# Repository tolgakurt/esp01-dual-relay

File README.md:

# Introduction

This project is about a dual channel relay circuit driven by an ESP8266-01 IC which connects to Azure IoT Hub. The device can be controlled by a progressive web app which communicates with serverless Azure functions in the backend which then communicates with the IoT Hub. We developed and built the circuit, and implemented the code nearly from scratch.  

This is a pet project and we aimed to build a nice gadget, but we also aimed to learn new things; so we implemented features and took precautions which are hardly necessary. So expect more detail than required. You may also find some already marketed products for that purpose, but they lack this feature or that we think that we must have, and moreover, where is the fun using such a product directly?  

This project began when we first encountered a specific type of curtain which is opened and closed by an AC motor. If you haven't encountered them yet, there are curtains which are like projector curtains in shape, which also include a cylindirical motor in the shaft that collects the curtain which can turn both ways depending on which input line of the motor is connected to AC phase line. The motor has 4 connections: 1 for ground, 1 for neutral, 2 for phase. One of the phase connections rotates the motor clock-wise and the other rotates anti clock-wise. So, why not develop a circuit that controls this curtain?  

We implemented this project with [Kutalmış İnce](http://kutalmisince.com/) and mobilized the curtains in our bedrooms so that they can be dynamically programmed by a mobile app to open up at (say) 7AM (best way to wake up gracefully) and close down at (say) 6PM, or can be opened or closed at the moment. We also wanted them to be manually controllable via simple switches. This became a long journey in which we first developed a master/slave configuration where a Raspberry Pi acted as the main hub directing some Atmel based controllers. We would put Raspberry Pi in close proximity of the router so that it can be accessed online, and it will connect with the controllers using nRF24L01+ ICs. However it became a bit expensive, and we thought that we could construct the same system using ESP8266 so that we get rid of slave/master configuration. This was cheaper and working, but we were using nodeMCU devboards (which use ESP8266-12 IC with lots of GPIO pins) and this could still get cheaper by using ESP8266-01 modules. This wasn't easy as said, since ESP8266-01 is a very limited and delicate (and almost unstable) module. Rest of this document and other documents in the folders explains the whole procedure to get such a system up and running steady.  

We tried to be sure about all the components we used and each line of code we wrote, but please comment if you notice something wrong or inappropriate. Needless to say, what we developed is a relay circuit controlled online, which means you can control any common AC (or DC, for that matter) utility with it.  

## The Circuit

We modeled the circuit using EAGLE. The details about the design and implementation of the circuit can be found in `pcb` folder. This folder also contains gcode files so that you can etch the pcb using a CNC machine. You can export the trace masks from EAGLE as well. More information can be found [here](pcb).  

## Embedded Code and Azure IoT Hub 

Embedded code is contained in `esp` folder. This software connects the device to Azure IoT Hub using MQTT protocol. An overall and detailed information can be found [here](esp).  

## Azure Functions and Storage

Azure Functions are implemented to handle user requests and manage the devices in the IoT Hub. All related files are in `azureFunctions` folder. The details about Azure Functions, related Azure Storage, and implemented API endpoints are defined [here](azureFunctions).  

## User Interface

A frontend for the users is implemented as a progressive web app. Frontend files are in `frontend` folder. The usage details and business logic of the user interface are explained [here](frontend).  

## Possible Enhancements

1. Use a 5V power supply and design a 3V3 voltage regulator phase (using LM1117-3V3) to power up ESP-01. At the current version, the main source of the instability of the circuit is the voltage spikes generated by the relay coils when they are triggered and released. Now, a zener-rectifier combination is used to dissipate coil charge and a zener-capacitor combination is used to smooth and clamp the voltage before ESP-01. However, a regulator will do that better than a zener-capacitor couple. (And according to a rumor, 5V relays create less spikes when they are triggered and released.) However, this change also effects the driving transistors. When the GPIO pins are high, they are 3V3. But the relays should be triggered using 5V. If we use a single PNP in that condition, the transistor will always be open since (5V - 3V3 = 1V7 > 0V6). So, we need to shift 3V3 to 5V with a Sziklai pair, where the first transistor is a PNP fed with 3V3 and triggers the base of the second transistor which is an NPN which is fed with 5V and drives the relays. On the other side, this configuration will render diodes connected to the GPIO pins useless, so we can get rid of them.  

2. No matter how well the code is written and how reliable the electronic components and the design, the circuit can become unresponsive after a while for this or that reason. So, an additional hardware watchdog built with 555 may restart the device in such a condition. A good design can be found [here](http://upperbound.com/projects/555-watchdog-timer/). Basically, what we need to do is to trigger 555 periodically from ESP-01 so that its countdown timer is reset. If we don't, it will trigger the `RST` pin of the ESP-01 after a while, which will cause a hard reset and the device hopefully becomes responsive again. The countdown resetting signal should be done as a result of a successful `pong` for a `ping` to Azure IoT Hub, so that we ensure that the device will restart if the device loses connection with Azure IoT Hub. However, there may be internet disconnections for a while, so we should let the hardware watchdog wait for a reasonable amount time before it restarts ESP-01.

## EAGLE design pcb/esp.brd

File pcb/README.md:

# The Schematic

We modeled the circuit using EAGLE. However, the devices used in the circuit model file is coming from my custom devices library. You need to have this library introduced to EAGLE beforehand. The library can be found [here](https://github.com/tolgakurt/eagle-parts-library).  

The schematic of the circuit is as such:  

## AC Line

The circuit does not include a power supply, so you need to have a 3.3V DC output power supply rated with at least 500mA. We are using [this circuit](https://www.banggood.com/AC-DC-3_5W-Isolated-AC-110V-220V-To-DC-3_3V-1A-Switch-Power-Supply-Converter-Module-p-1088504.html?rmmds=buy&cur_warehouse=CN). You need to connect your AC line to the `ACIN` connector and you can also connect parallel cables to the input rail of the power supply from `ACIN`. `ACOUT` connector will deliver power up to two devices. We use one pin in `ACOUT` connector to open the curtain, and the other to close. The last one goes to the neutral line of the motor. You can also use one more pin in each connector to connect the ground cable.  

## DC Line

As I mentioned, the power is supplied by an external circuit. This circuit has a single input at `3V3IN` connector for all the components. Generally it is a better practice to isolate the relays from the driver circuit because of the voltage spikes generated by the coil in the relay with the help of an optocoupler, but this necessitates a secondary power source. However, we wanted to keep this simple and cheap. More on spike protection below.  

## Powering Up ESP-01

ESP-01 is a small and cheap IC, and has only 2 GPIO pins which is barely enough for a simple project like this. Moreover, these IO pins are also used to determine the boot mode. More on this subject [here](https://www.forward.com.au/pfod/ESP8266/GPIOpins/ESP8266_01_pin_magic.html).  

Basically, you need to pull both IO pins high to boot from SPI flash (which is the normal operating mode). So, you need to connect these pins to 3V3 rail using resistors. In the article linked above, 3K3 resistors are adviced, however, during our tests, We found out that 3K3 may not be strong enough to pull IO pins high. Using 3K3, something like 1 in 10, ESP-01 couldn't start from SPI flash. So, we tried again using 2K2, and found that it always booted correctly. We are not entirely sure about the reason, please correct us on this if we're mistaken.  

You need to connect `VCC` pin to 3V3 rail and GND pin to ground directly. It is also a good practice to pull `CH_PD` and `RST` pin high, so we connected them to 3V3 rail via 3K3 resistors. Moreover to that, we connected `RST` pin to ground via a 100uF capacitor to prevent the device from boot during power up phase for a short period, till the supply rail becomes steady. Also, `SWRST+` pin is connected to `RST` pin, so that you can connect a switch in between this and `SWRST-` pin and reset the device with that.  

The GPIO pins are used to drive the relays, but we also needed an input to reset the WiFi configuration of the ESP-01 in case of a configuration change in WiFi. So, we used `RX` pin as a pullup input. When `RX` pin is initialized as `INPUT_PULLUP`, it is internally pulled high weakly. To be sure, we also connected it to 3V3 rail with a 3K3 resistor. If you connect a switch in between `SWRX+` pin and `SWRX-` and close this switch, RX pin will read low and then you can reset the WiFi configuration. A pin is also connected to `TX` to be able to connect to the device and view the logs in serial monitor while debugging.  

In addition to the power supply, it is always a good practice to put some decoupling capacitors close to `VCC` and `GND` pins of ESP-01, so we included a 15pF and a 100nF capacitors. More than that, we observed that the power supply cannot function steadily when the relays are clicking, so we placed a 220uF capacitor and a 3V3 zener parallel to the decoupling capacitors to clamp and smooth the voltage spikes which dramatically enhanced the stability of ESP-01.  

## Driving Relays

ESP-01 cannot drive the relays directly since it can source only 12mA current, which is not enough to activate the relays. So, there needs to be a transistor in between to control the current over the relays, and these transistors need to be PNP type because their base are connected to GPIO pins which are inevitably connected to 3V3. In this configuration, `IO0` and `IO2` are pulled high in the beginning of ESP-01 `setup` function and when a relay needs to be activated, connected GPIO pin is pulled low.  

At first, we were driving the relays using only the transistors and ESP-01, but we thought that it would be nice to have some buttons or switches, which can also control the relays in parallel to ESP-01. This is somehow a very handy feature since your ESP-01 may become bricked or you cannot (or don't want to) reach ESP-01 over WiFi. `SW1+` and `SW2+` pins are introduced for this reason. So that, you can connect a switch in between these pins and `SW12-` pin, which goes to ground, and pull the base of the transistors low and activate the transistors. But you need to prevent the current flowing from `IO0` and `IO2` to ground. For this reason, there are `D1` and `D2` in between, which prevents flow in that direction.  

The relays we used are triggered at 3V and they use a current of 105mA to operate. For the spike protection, we used a reverse-biased diode in combination with a 3V3 zener. Generally, a single diode is advised, but an additional zener helps to extend relay life as described [here](https://www.te.com/commerce/DocumentDelivery/DDEController?Action=srchrtrv&DocNm=13C3264_AppNote&DocType=CS&DocLang=EN).  

Parallel to the relays and spike suppression components, there is a low-power led, which is used to indicate if the relay is switched on. These leds are known to have a forward voltage of 2.0V, so they will leave 1.3V behind. They need a current in between 5-20mA, so a 100R resistor will let 13mA to pass, which is OK.  

So, we require a total current of about 120mA and the transistors should let that. We used 2N3906 transistors since they can support a collector current of 200mA continuously. They are commonly found and are very cheap. You can also use something like 2N2222 which lets 1A to pass. But beware of using some other commonly found transistors like BC557 since they are rated as 100mA max.  

We will use these transistors not in linear region, but in saturation mode as simple switches. So, we need to determine the base current using the gain characteristics of 2N3906. [In its datasheet](https://www.sparkfun.com/datasheets/Components/2N3906.pdf), it says that the minimum gain is 30 when the collector is at 100mA and Vce is 1V. We access the base via a diode, so we have a drop of 0.7V there. The base needs to be 0.7V lower than the emitter. Thus we have 3.3V - 0.7V - 0.7V = 1.9V left. This is close to 1V, so we will assume the minimum gain suggested in the specs: 30.  

We need to have a current of 120mA in the collector, thus we need 4mA in the base which can be ensured with a 470R base resistor. On the other hand, 4mA is safely less than 12mA, which is the recommended sink current limit of ESP-01 GPIO pins.  

The switch does not pass over a diode as the GPIO pins, so it will introduce slightly more current to the base, which is not a problem.  

# The Board

As I mentioned, the components used in the circuit model file is coming from my custom devices library. I developed this library to create custom packages that fits [my custom made CNC machine](https://github.com/tolgakurt/my-custom-cnc). DRC rules, pad diameters, trace widths are all set according to the specs of this machine. Finally, the board we created is for a single-sided PCB and looks as such:  

Let me remind you that this circuit involves high voltage AC application, so please take necessary precautions before getting your hands dirty.  

## Etching

`.sch` and `.brd` files are in this directory, so you can create the etching mask if you are using chemicals to create the nets. We used my custom made CNC machine, so we generated gcode using the `PCB-GCode` plugin. You can find related information [here](http://www.richa1.com/RichardAlbritton/create-g-code-from-an-eagle-file/). The gcode generated by this plugin is also given in `gcode` folder. You can use them if somehow your device is similar to mine.  

The teal colored lines represent the milling routes with 0.5mm of depth and 1mm of width. These lines are used to isolate the AC line from the DC part better. They also isolate AC lines from each other. With these lines in place, you can actually delete the trace lines carrying AC.  

The same teal colored lines also indicate the outer frame, so you may need to modify gcode to change the depth of these outer lines to 1.5mm, so that the circuit can be cut out of the whole PCB.  

The board fits in a frame of size 36mm by 60mm. We used male pins to connect push buttons and switches (which are not embedded on PCB, but placed on a 3D printed box), and DC. Likewise we used female pin plugs to connect ESP-01. This way, we can put the ESP-01 up above other components saving up space. We used 5mm connectors to connect AC rails which are directly soldered into the board. You can separate them as well.  

These photos are from an earlier iteration and does not fully represent the board given above; but they will represent the idea more or less:

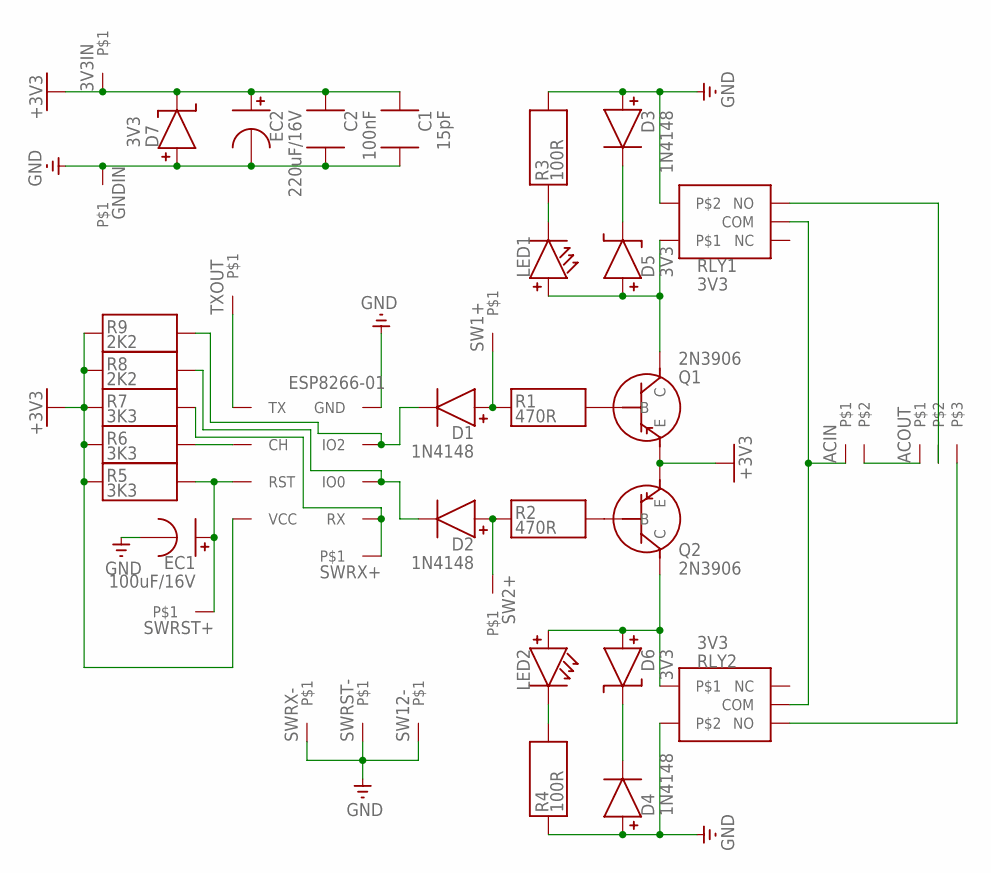
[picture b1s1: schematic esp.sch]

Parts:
3V3IN: CON1PINPLUG1; PINPLUG1
ACIN: CON2CON5.0S2T; CON5.0S2T
ACOUT: CON3CON5.0S3T; CON5.0S3T
C1: 15pF; CERCAP3.2S
C2: 100nF; CERCAP5.6S
D1, D2, D3, D4: 1N4148; RD5.0S1.8D
D5, D6, D7: 3V3; ZD6.0S2.0D
EC1: 100uF/16V; ECAP3.2S5.0D
EC2: 220uF/16V; ECAP3.2S5.0D
ESP8266-01: ESP8266E01ESP8266E01; ESP8266E01
GNDIN: CON1PINPLUG1; PINPLUG1
LED1, LED2: LEDLED3.2S5.0D; LED3.2S5.0D
Q1, Q2: 2N3906; TO92
R1, R2: 470R; HOR.25W
R3, R4: 100R; HOR.25W
R5, R6, R7: 3K3; HOR.25W
R8, R9: 2K2; HOR.25W
RLY1, RLY2: 3V3; RLY15W19L
SW1+, SW2+, SW12-: CON1PINPLUG1; PINPLUG1
SWRST+: CON1PINPLUG1; PINPLUG1
SWRST-: CON1PINPLUG1; PINPLUG1
SWRX+: CON1PINPLUG1; PINPLUG1
SWRX-: CON1PINPLUG1; PINPLUG1
TXOUT: CON1PINPLUG1; PINPLUG1

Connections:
+3V3: 3V3IN.P$1, C1.P$1, C2.P$1, D7.P-, EC2.P+, ESP8266-01.VCC, Q1.3 (E), Q2.3 (E), R5.P$1, R6.P$1, R7.P$1, R8.P$1, R9.P$1
GND: C1.P$2, C2.P$2, D3.P+, D4.P+, D7.P+, EC1.P-, EC2.P-, ESP8266-01.GND, GNDIN.P$1, R3.P$2, R4.P$1, RLY1.P$2, RLY2.P$2, SW12-.P$1, SWRST-.P$1, SWRX-.P$1
unnamed: LED2.P-, R4.P$2
unnamed: ESP8266-01.CH, R6.P$2
unnamed: ESP8266-01.RX, R7.P$2, SWRX+.P$1
unnamed: Q1.2 (B), R1.P$2
unnamed: D1.P+, R1.P$1, SW1+.P$1
unnamed: D2.P-, ESP8266-01.IO0, R8.P$2
unnamed: D6.P+, LED2.P+, Q2.1 (C), RLY2.P$1
unnamed: LED1.P-, R3.P$1
unnamed: D4.P-, D6.P-
unnamed: EC1.P+, ESP8266-01.RST, R5.P$2, SWRST+.P$1
unnamed: ACOUT.P$3, RLY2.NO
unnamed: D5.P+, LED1.P+, Q1.1 (C), RLY1.P$1
unnamed: ESP8266-01.TX, TXOUT.P$1
unnamed: D3.P-, D5.P-
unnamed: ACOUT.P$2, RLY1.NO
unnamed: ACIN.P$2, ACOUT.P$1
unnamed: Q2.2 (B), R2.P$2
unnamed: D2.P+, R2.P$1, SW2+.P$1
unnamed: ACIN.P$1, RLY1.COM, RLY2.COM
unnamed: D1.P-, ESP8266-01.IO2, R9.P$2

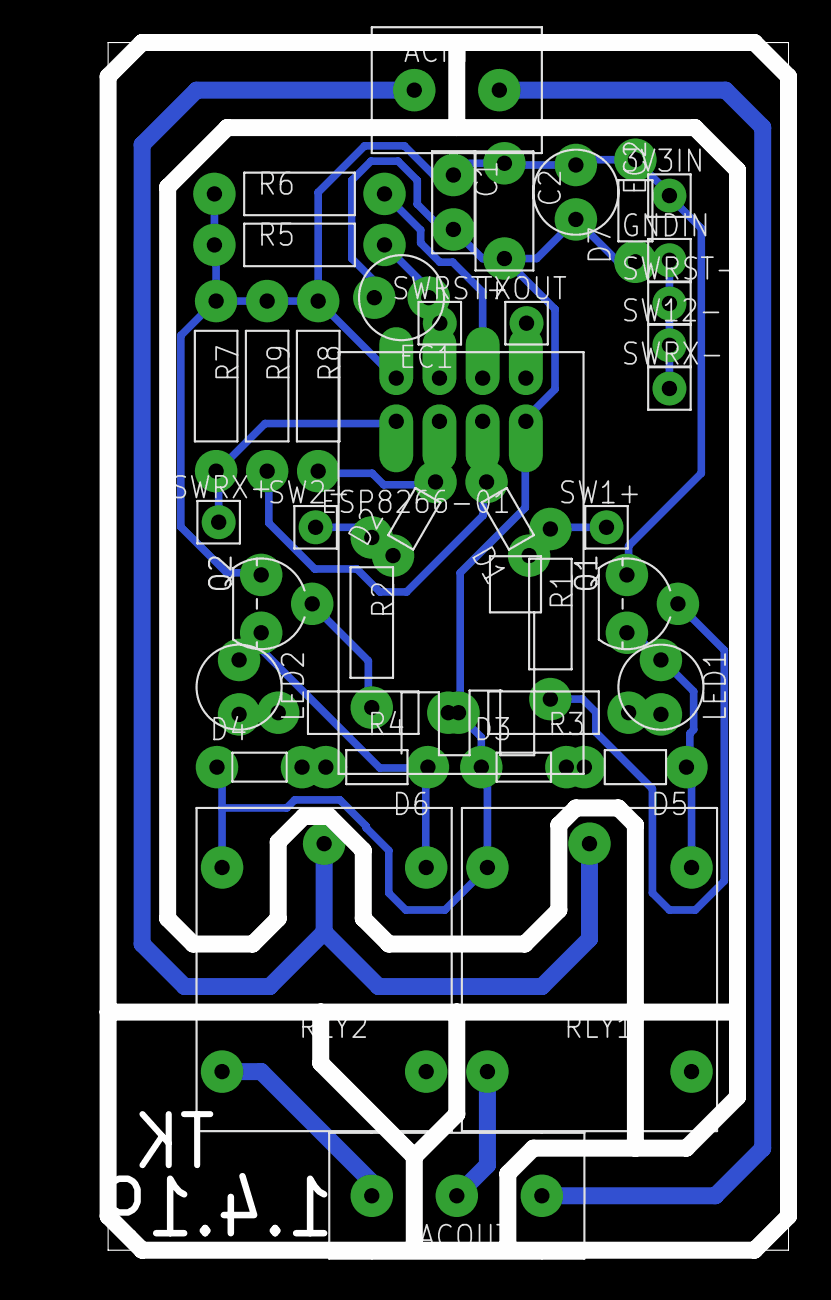
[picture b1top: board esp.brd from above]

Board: 2 copper layers, 40.0 x 71.0 mm, 39 parts (0 on the bottom side), 22 nets.

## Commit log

2018-12-18 Update README. Add gcode files. Add EAGLE model files. Add pictures.
2018-12-18 Set theme jekyll-theme-slate
2019-05-05 Add ignore files.
2019-05-07 Remove ignored EAGLE files. Separate the README files. Renew circuit schematic and board images.
2019-05-11 Add embedded software and its README.
2019-05-11 Add Azure Functions and related README. Ignore the file that should contain the connection strings to the Azure IoT Hub and Azure Storage.
2019-05-11 Add PWA frontend that is used to manage the devices from a browser and related README.
2019-05-11 Update main README and esp README.
2019-05-12 Link to folders, not to README files in main README file.
2020-03-12 Add a completely different side project: Arduino + DS1302 RTC + 16x2 LED Screen based, non-connecting control module.
